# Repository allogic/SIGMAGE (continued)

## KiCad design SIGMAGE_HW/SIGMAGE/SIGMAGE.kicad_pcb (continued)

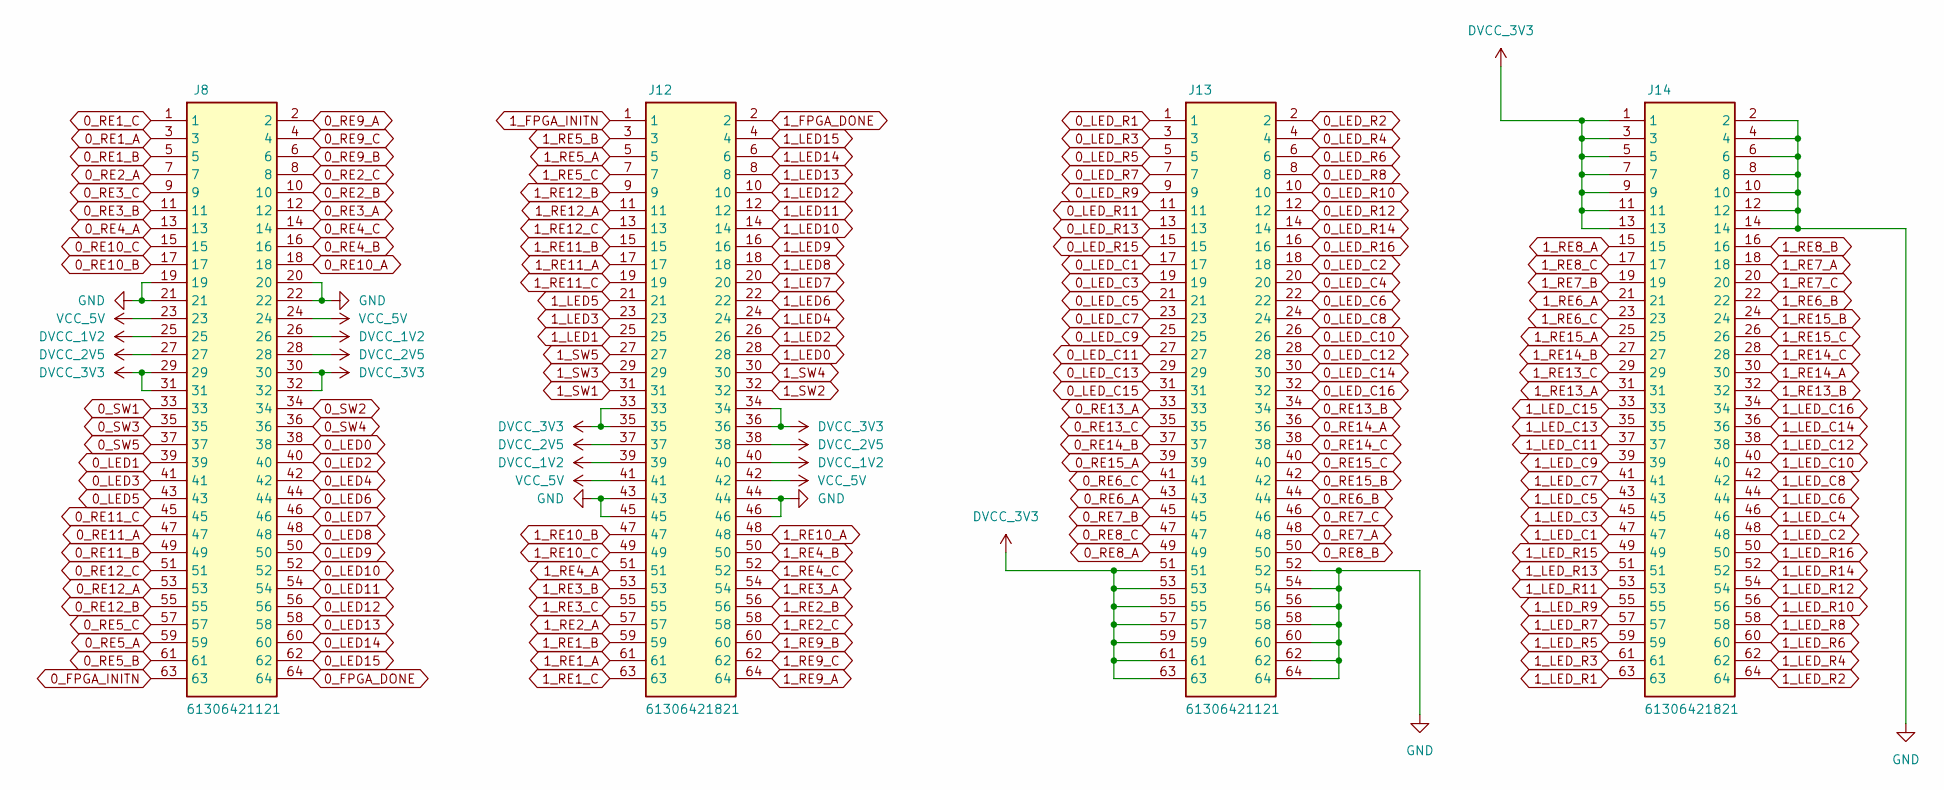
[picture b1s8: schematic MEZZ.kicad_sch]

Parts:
J8, J13: 61306421121; Manufacturer_Part_Number 61306421121; Mouser Part Number 710-61306421121
J12, J14: 61306421821; Manufacturer_Part_Number 61306421821; Mouser Part Number 710-61306421821

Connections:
0_FPGA_DONE: J8.64; also elsewhere on the board
0_FPGA_INITN: J8.63; also elsewhere on the board
0_LED0: J8.38; also elsewhere on the board
0_LED1: J8.39; also elsewhere on the board
0_LED2: J8.40; also elsewhere on the board
0_LED3: J8.41; also elsewhere on the board
0_LED4: J8.42; also elsewhere on the board
0_LED5: J8.43; also elsewhere on the board
0_LED6: J8.44; also elsewhere on the board
0_LED7: J8.46; also elsewhere on the board
0_LED8: J8.48; also elsewhere on the board
0_LED9: J8.50; also elsewhere on the board
0_LED10: J8.52; also elsewhere on the board
0_LED11: J8.54; also elsewhere on the board
0_LED12: J8.56; also elsewhere on the board
0_LED13: J8.58; also elsewhere on the board
0_LED14: J8.60; also elsewhere on the board
0_LED15: J8.62; also elsewhere on the board
0_LED_C1: J13.17; also elsewhere on the board
0_LED_C2: J13.18; also elsewhere on the board
0_LED_C3: J13.19; also elsewhere on the board
0_LED_C4: J13.20; also elsewhere on the board
0_LED_C5: J13.21; also elsewhere on the board
0_LED_C6: J13.22; also elsewhere on the board
0_LED_C7: J13.23; also elsewhere on the board
0_LED_C8: J13.24; also elsewhere on the board
0_LED_C9: J13.25; also elsewhere on the board
0_LED_C10: J13.26; also elsewhere on the board
0_LED_C11: J13.27; also elsewhere on the board
0_LED_C12: J13.28; also elsewhere on the board
0_LED_C13: J13.29; also elsewhere on the board
0_LED_C14: J13.30; also elsewhere on the board
0_LED_C15: J13.31; also elsewhere on the board
0_LED_C16: J13.32; also elsewhere on the board
0_LED_R1: J13.1; also elsewhere on the board
0_LED_R2: J13.2; also elsewhere on the board
0_LED_R3: J13.3; also elsewhere on the board
0_LED_R4: J13.4; also elsewhere on the board
0_LED_R5: J13.5; also elsewhere on the board
0_LED_R6: J13.6; also elsewhere on the board
0_LED_R7: J13.7; also elsewhere on the board
0_LED_R8: J13.8; also elsewhere on the board
0_LED_R9: J13.9; also elsewhere on the board
0_LED_R10: J13.10; also elsewhere on the board
0_LED_R11: J13.11; also elsewhere on the board
0_LED_R12: J13.12; also elsewhere on the board
0_LED_R13: J13.13; also elsewhere on the board
0_LED_R14: J13.14; also elsewhere on the board
0_LED_R15: J13.15; also elsewhere on the board
0_LED_R16: J13.16; also elsewhere on the board
0_RE1_A: J8.3; also elsewhere on the board
0_RE1_B: J8.5; also elsewhere on the board
0_RE1_C: J8.1; also elsewhere on the board
0_RE2_A: J8.7; also elsewhere on the board
0_RE2_B: J8.10; also elsewhere on the board
0_RE2_C: J8.8; also elsewhere on the board
0_RE3_A: J8.12; also elsewhere on the board
0_RE3_B: J8.11; also elsewhere on the board
0_RE3_C: J8.9; also elsewhere on the board
0_RE4_A: J8.13; also elsewhere on the board
0_RE4_B: J8.16; also elsewhere on the board
0_RE4_C: J8.14; also elsewhere on the board
0_RE5_A: J8.59; also elsewhere on the board
0_RE5_B: J8.61; also elsewhere on the board
0_RE5_C: J8.57; also elsewhere on the board
0_RE6_A: J13.43; also elsewhere on the board
0_RE6_B: J13.44; also elsewhere on the board
0_RE6_C: J13.41; also elsewhere on the board
0_RE7_A: J13.48; also elsewhere on the board
0_RE7_B: J13.45; also elsewhere on the board
0_RE7_C: J13.46; also elsewhere on the board
0_RE8_A: J13.49; also elsewhere on the board
0_RE8_B: J13.50; also elsewhere on the board
0_RE8_C: J13.47; also elsewhere on the board
0_RE9_A: J8.2; also elsewhere on the board
0_RE9_B: J8.6; also elsewhere on the board
0_RE9_C: J8.4; also elsewhere on the board
0_RE10_A: J8.18; also elsewhere on the board
0_RE10_B: J8.17; also elsewhere on the board
0_RE10_C: J8.15; also elsewhere on the board
0_RE11_A: J8.47; also elsewhere on the board
0_RE11_B: J8.49; also elsewhere on the board
0_RE11_C: J8.45; also elsewhere on the board
0_RE12_A: J8.53; also elsewhere on the board
0_RE12_B: J8.55; also elsewhere on the board
0_RE12_C: J8.51; also elsewhere on the board
0_RE13_A: J13.33; also elsewhere on the board
0_RE13_B: J13.34; also elsewhere on the board
0_RE13_C: J13.35; also elsewhere on the board
0_RE14_A: J13.36; also elsewhere on the board
0_RE14_B: J13.37; also elsewhere on the board
0_RE14_C: J13.38; also elsewhere on the board
0_RE15_A: J13.39; also elsewhere on the board
0_RE15_B: J13.42; also elsewhere on the board
0_RE15_C: J13.40; also elsewhere on the board
0_SW1: J8.33; also elsewhere on the board
0_SW2: J8.34; also elsewhere on the board
0_SW3: J8.35; also elsewhere on the board
0_SW4: J8.36; also elsewhere on the board
0_SW5: J8.37; also elsewhere on the board
1_FPGA_DONE: J12.2; also elsewhere on the board
1_FPGA_INITN: J12.1; also elsewhere on the board
1_LED0: J12.28; also elsewhere on the board
1_LED1: J12.25; also elsewhere on the board
1_LED2: J12.26; also elsewhere on the board
1_LED3: J12.23; also elsewhere on the board
1_LED4: J12.24; also elsewhere on the board
1_LED5: J12.21; also elsewhere on the board
1_LED6: J12.22; also elsewhere on the board
1_LED7: J12.20; also elsewhere on the board
1_LED8: J12.18; also elsewhere on the board
1_LED9: J12.16; also elsewhere on the board
1_LED10: J12.14; also elsewhere on the board
1_LED11: J12.12; also elsewhere on the board
1_LED12: J12.10; also elsewhere on the board
1_LED13: J12.8; also elsewhere on the board
1_LED14: J12.6; also elsewhere on the board
1_LED15: J12.4; also elsewhere on the board
1_LED_C1: J14.47; also elsewhere on the board
1_LED_C2: J14.48; also elsewhere on the board
1_LED_C3: J14.45; also elsewhere on the board
1_LED_C4: J14.46; also elsewhere on the board
1_LED_C5: J14.43; also elsewhere on the board
1_LED_C6: J14.44; also elsewhere on the board
1_LED_C7: J14.41; also elsewhere on the board
1_LED_C8: J14.42; also elsewhere on the board
1_LED_C9: J14.39; also elsewhere on the board
1_LED_C10: J14.40; also elsewhere on the board
1_LED_C11: J14.37; also elsewhere on the board
1_LED_C12: J14.38; also elsewhere on the board
1_LED_C13: J14.35; also elsewhere on the board
1_LED_C14: J14.36; also elsewhere on the board
1_LED_C15: J14.33; also elsewhere on the board
1_LED_C16: J14.34; also elsewhere on the board
1_LED_R1: J14.63; also elsewhere on the board
1_LED_R2: J14.64; also elsewhere on the board
1_LED_R3: J14.61; also elsewhere on the board
1_LED_R4: J14.62; also elsewhere on the board
1_LED_R5: J14.59; also elsewhere on the board
1_LED_R6: J14.60; also elsewhere on the board
1_LED_R7: J14.57; also elsewhere on the board
1_LED_R8: J14.58; also elsewhere on the board
1_LED_R9: J14.55; also elsewhere on the board
1_LED_R10: J14.56; also elsewhere on the board
1_LED_R11: J14.53; also elsewhere on the board
1_LED_R12: J14.54; also elsewhere on the board
1_LED_R13: J14.51; also elsewhere on the board
1_LED_R14: J14.52; also elsewhere on the board
1_LED_R15: J14.49; also elsewhere on the board
1_LED_R16: J14.50; also elsewhere on the board
1_RE1_A: J12.61; also elsewhere on the board
1_RE1_B: J12.59; also elsewhere on the board
1_RE1_C: J12.63; also elsewhere on the board
1_RE2_A: J12.57; also elsewhere on the board
1_RE2_B: J12.56; also elsewhere on the board
1_RE2_C: J12.58; also elsewhere on the board
1_RE3_A: J12.54; also elsewhere on the board
1_RE3_B: J12.53; also elsewhere on the board
1_RE3_C: J12.55; also elsewhere on the board
1_RE4_A: J12.51; also elsewhere on the board
1_RE4_B: J12.50; also elsewhere on the board
1_RE4_C: J12.52; also elsewhere on the board
1_RE5_A: J12.5; also elsewhere on the board
1_RE5_B: J12.3; also elsewhere on the board
1_RE5_C: J12.7; also elsewhere on the board
1_RE6_A: J14.21; also elsewhere on the board
1_RE6_B: J14.22; also elsewhere on the board
1_RE6_C: J14.23; also elsewhere on the board
1_RE7_A: J14.18; also elsewhere on the board
1_RE7_B: J14.19; also elsewhere on the board
1_RE7_C: J14.20; also elsewhere on the board
1_RE8_A: J14.15; also elsewhere on the board
1_RE8_B: J14.16; also elsewhere on the board
1_RE8_C: J14.17; also elsewhere on the board
1_RE9_A: J12.64; also elsewhere on the board
1_RE9_B: J12.60; also elsewhere on the board
1_RE9_C: J12.62; also elsewhere on the board
1_RE10_A: J12.48; also elsewhere on the board
1_RE10_B: J12.47; also elsewhere on the board
1_RE10_C: J12.49; also elsewhere on the board
1_RE11_A: J12.17; also elsewhere on the board
1_RE11_B: J12.15; also elsewhere on the board
1_RE11_C: J12.19; also elsewhere on the board
1_RE12_A: J12.11; also elsewhere on the board
1_RE12_B: J12.9; also elsewhere on the board
1_RE12_C: J12.13; also elsewhere on the board
1_RE13_A: J14.31; also elsewhere on the board
1_RE13_B: J14.32; also elsewhere on the board
1_RE13_C: J14.29; also elsewhere on the board
1_RE14_A: J14.30; also elsewhere on the board
1_RE14_B: J14.27; also elsewhere on the board
1_RE14_C: J14.28; also elsewhere on the board
1_RE15_A: J14.25; also elsewhere on the board
1_RE15_B: J14.24; also elsewhere on the board
1_RE15_C: J14.26; also elsewhere on the board
1_SW1: J12.31; also elsewhere on the board
1_SW2: J12.32; also elsewhere on the board
1_SW3: J12.29; also elsewhere on the board
1_SW4: J12.30; also elsewhere on the board
1_SW5: J12.27; also elsewhere on the board
DVCC_1V2: J8.25, J8.26, J12.39, J12.40; also elsewhere on the board
DVCC_2V5: J8.27, J8.28, J12.37, J12.38; also elsewhere on the board
DVCC_3V3: J8.29, J8.30, J8.31, J8.32, J12.33, J12.34, J12.35, J12.36, J13.51, J13.53, J13.55, J13.57, J13.59, J13.61, J13.63, J14.1, J14.3, J14.5, J14.7, J14.9, J14.11, J14.13; also elsewhere on the board
GND: J8.19, J8.20, J8.21, J8.22, J12.43, J12.44, J12.45, J12.46, J13.52, J13.54, J13.56, J13.58, J13.60, J13.62, J13.64, J14.2, J14.4, J14.6, J14.8, J14.10, J14.12, J14.14; also elsewhere on the board

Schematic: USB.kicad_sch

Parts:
C10, C11: 2.2u; C_0603_1608Metric
C33, C35: 4700n; C_0603_1608Metric
C34, C36, C38, C39, C40, C41, C42, C43, C44, C46: 100n; C_0603_1608Metric
C37, C45: 10u; C_0603_1608Metric
C47, C48: 18p; C_0603_1608Metric
CR1: 7M12MAAJT
D4: LED; LED_0603_1608Metric
FB4: 500 @ 100 MHz; C_0603_1608Metric
FB6, FB7: 600 @ 100 MHz; C_0603_1608Metric
J1: UJ31CHG2SMTTR; Manufacturer_Part_Number UJ31-CH-G2-SMT-TR; Mouser Part Number 490-UJ31-CH-G2SMT-TR
J3, J6: TSW10607GS
R10, R11: 5k1; R_0603_1608Metric
R12: 1500; R_0603_1608Metric
R22, R26, R27: 10k; R_0603_1608Metric
R28, R29, R30, R31, R59, R60, R61, R62: 4700; R_0603_1608Metric
R41, R43: 12k; R_0603_1608Metric
R42: 2200; R_0603_1608Metric
U9: FT2232HLTRAY; FT2232HTRAY
U13: ESDR0502NMUTBG
U14: 93LC56-I/SN; 93LC56ISN

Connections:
0_FPGA_JTAG_TCK: J3.5, R28.2, U9.16 (ADBUS0); also elsewhere on the board
0_FPGA_JTAG_TDI: J3.4, R29.1, U9.17 (ADBUS1); also elsewhere on the board
0_FPGA_JTAG_TDO: J3.3, R30.1, U9.18 (ADBUS2); also elsewhere on the board
0_FPGA_JTAG_TMS: J3.2, R31.1, U9.19 (ADBUS3); also elsewhere on the board
0_MCU_JTAG_TCK: J6.5, R60.2, U9.38 (BDBUS0); also elsewhere on the board
0_MCU_JTAG_TDI: J6.4, R59.1, U9.39 (BDBUS1); also elsewhere on the board
0_MCU_JTAG_TDO: J6.3, R61.1, U9.40 (BDBUS2); also elsewhere on the board
0_MCU_JTAG_TMS: J6.2, R62.1, U9.41 (BDBUS3); also elsewhere on the board
0_USB_DN: J1.A7 (DN1), J1.B7 (DN2), U9.7 (DM), U13.3 (NC), U13.4 (D-)
0_USB_DP: J1.A6 (DP1), J1.B6 (DP2), U9.8 (DP), U13.2 (NC), U13.5 (D+)
DVCCFT_1V8: C37.1, C38.1, C39.1, C40.1, U9.12 (VCORE), U9.37 (VCORE), U9.49 (VREGOUT), U9.64 (VCORE)
DVCC_3V3: C41.1, C42.1, C43.1, C44.1, C45.1, C46.1, FB6.1, FB7.1, J3.1, J6.1, R22.2, R26.2, R27.2, R29.2, R30.2, R31.2, R42.1, R59.2, R61.2, R62.2, U9.20 (VCCIO), U9.31 (VCCIO), U9.42 (VCCIO), U9.50 (VREGIN), U9.56 (VCCIO), U14.6 (ORG), U14.8 (VCC); also elsewhere on the board
GND: C10.2, C11.2, C33.2, C34.2, C35.2, C36.2, C37.2, C38.2, C39.2, C40.2, C41.2, C42.2, C43.2, C44.2, C45.2, C46.2, C47.2, C48.2, CR1.2, CR1.4, D4.1 (K), J1.A1 (GND_1), J1.A12 (GND_2), J1.B1 (GND_3), J1.B12 (GND_4), J1.S1 (GND_5), J1.S2 (GND_6), J1.S3 (GND_7), J1.S4 (GND_8), J3.6, J6.6, R10.2, R11.2, R28.1, R41.1, R60.1, U9.1 (GND), U9.5 (GND), U9.10 (AGND), U9.11 (GND), U9.13 (TEST), U9.15 (GND), U9.25 (GND), U9.35 (GND), U9.47 (GND), U9.51 (GND), U13.1 (GND), U14.5 (VSS); also elsewhere on the board
unnamed: D4.2 (A), R12.2
unnamed: J1.A5 (CC1), R10.1
unnamed: J1.B5 (CC2), R11.1
unnamed: C47.1, CR1.1, U9.2 (OSCI)
unnamed: C48.1, CR1.3, U9.3 (OSCO)
unnamed: R41.2, U9.6 (REF)
unnamed: R42.2, U9.14 (RESET#)
unnamed: C33.1, C34.1, FB6.2, U9.4 (VPHY)
unnamed: C35.1, C36.1, FB7.2, U9.9 (VPLL)
unnamed: R26.1, U9.62 (EECLK), U14.2 (CLK)
unnamed: R22.1, U9.63 (EECS), U14.1 (CS)
unnamed: R43.2, U9.61 (EEDATA), U14.3 (DI)
unnamed: R27.1, R43.1, U14.4 (DO)

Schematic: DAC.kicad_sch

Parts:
C58, C60, C66, C68, C72, C73, C76, C77, C145, C146, C147, C148, C153, C154, C155, C156: 10u; C_0603_1608Metric
C59, C61, C67, C69, C74, C75, C78, C79, C149, C150, C151, C152, C157, C158, C159, C160: 100n; C_0603_1608Metric
C62, C63, C82, C83, C165, C166, C167, C168: 1u; C_0603_1608Metric
C64, C65, C80, C81, C161, C162, C163, C164: 2200n; C_0603_1608Metric
C70, C71, C84, C85, C169, C170, C171, C172: 1n; C_0603_1608Metric
J20, J21, J24, J25: SJ63073E; Manufacturer_Part_Number SJ-63073E; Mouser Part Number 490-SJ-63073E
R33, R34, R39, R40, R63, R64, R65, R66: 6500; R_0603_1608Metric
R35, R36, R37, R38, R52, R53, R54, R55: 1M; R_0603_1608Metric
U3, U10, U20, U21: PCM5102APWR

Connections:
0_BUS_DAC_BCK: U3.13 (BCK), U10.13 (BCK), U20.13 (BCK), U21.13 (BCK); also elsewhere on the board
0_BUS_DAC_LRCK: U3.15 (LRCK), U10.15 (LRCK), U20.15 (LRCK), U21.15 (LRCK); also elsewhere on the board
0_BUS_DAC_SCK: U3.12 (SCK), U10.12 (SCK), U20.12 (SCK), U21.12 (SCK); also elsewhere on the board
0_DAC1_DIN: U3.14 (DIN); also elsewhere on the board
0_DAC1_FLT: U3.11 (FLT); also elsewhere on the board
0_DAC1_XSMT: U3.17 (XSMT); also elsewhere on the board
0_DAC2_DIN: U10.14 (DIN); also elsewhere on the board
0_DAC2_FLT: U10.11 (FLT); also elsewhere on the board
0_DAC2_XSMT: U10.17 (XSMT); also elsewhere on the board
0_DAC3_DIN: U20.14 (DIN); also elsewhere on the board
0_DAC3_FLT: U20.11 (FLT); also elsewhere on the board
0_DAC3_XSMT: U20.17 (XSMT); also elsewhere on the board
0_DAC4_DIN: U21.14 (DIN); also elsewhere on the board
0_DAC4_FLT: U21.11 (FLT); also elsewhere on the board
0_DAC4_XSMT: U21.17 (XSMT); also elsewhere on the board
AVCC_3V3: C66.1, C67.1, C68.1, C69.1, C72.1, C73.1, C74.1, C75.1, C145.1, C146.1, C147.1, C148.1, C149.1, C150.1, C151.1, C152.1, U3.1 (CPVDD), U3.8 (AVDD), U10.1 (CPVDD), U10.8 (AVDD), U20.1 (CPVDD), U20.8 (AVDD), U21.1 (CPVDD), U21.8 (AVDD); also elsewhere on the board
DVCC_3V3: C60.1, C61.1, C77.1, C79.1, C154.1, C156.1, C158.1, C160.1, U3.20 (DVDD), U10.20 (DVDD), U20.20 (DVDD), U21.20 (DVDD); also elsewhere on the board
GND: C58.2, C59.2, C60.2, C61.2, C65.2, C66.2, C67.2, C68.2, C69.2, C70.2, C71.2, C72.2, C73.2, C74.2, C75.2, C76.2, C77.2, C78.2, C79.2, C81.2, C84.2, C85.2, C145.2, C146.2, C147.2, C148.2, C149.2, C150.2, C151.2, C152.2, C153.2, C154.2, C155.2, C156.2, C157.2, C158.2, C159.2, C160.2, C162.2, C164.2, C169.2, C170.2, C171.2, C172.2, J20.1 (SLEEVE), J21.1 (SLEEVE), J24.1 (SLEEVE), J25.1 (SLEEVE), R35.1, R36.1, R37.1, R38.1, R52.1, R53.1, R54.1, R55.1, U3.3 (CPGND), U3.9 (AGND), U3.10 (DEMP), U3.16 (FMT), U3.19 (DGND), U10.3 (CPGND), U10.9 (AGND), U10.10 (DEMP), U10.16 (FMT), U10.19 (DGND), U20.3 (CPGND), U20.9 (AGND), U20.10 (DEMP), U20.16 (FMT), U20.19 (DGND), U21.3 (CPGND), U21.9 (AGND), U21.10 (DEMP), U21.16 (FMT), U21.19 (DGND); also elsewhere on the board
unnamed: C62.2, R33.1, R35.2
unnamed: C63.2, R34.1, R36.2
unnamed: C82.2, R37.2, R39.1
unnamed: C83.2, R38.2, R40.1
unnamed: C165.2, R52.2, R63.1
unnamed: C166.2, R53.2, R64.1
unnamed: C167.2, R54.2, R65.1
unnamed: C168.2, R55.2, R66.1
unnamed: C71.1, J20.3 (RING), R34.2
unnamed: C70.1, J20.2 (TIP), R33.2
unnamed: C85.1, J21.3 (RING), R40.2
unnamed: C84.1, J21.2 (TIP), R39.2
unnamed: C170.1, J24.3 (RING), R64.2
unnamed: C169.1, J24.2 (TIP), R63.2
unnamed: C172.1, J25.3 (RING), R66.2
unnamed: C171.1, J25.2 (TIP), R65.2
unnamed: C64.2, U3.4 (CAPM)
unnamed: C64.1, U3.2 (CAPP)
unnamed: C58.1, C59.1, U3.18 (LDOO)
unnamed: C62.1, U3.6 (OUTL)
unnamed: C63.1, U3.7 (OUTR)
unnamed: C65.1, U3.5 (VNEG)
unnamed: C80.2, U10.4 (CAPM)
unnamed: C80.1, U10.2 (CAPP)
unnamed: C76.1, C78.1, U10.18 (LDOO)
unnamed: C82.1, U10.6 (OUTL)
unnamed: C83.1, U10.7 (OUTR)
unnamed: C81.1, U10.5 (VNEG)
unnamed: C161.2, U20.4 (CAPM)
unnamed: C161.1, U20.2 (CAPP)
unnamed: C153.1, C157.1, U20.18 (LDOO)
unnamed: C165.1, U20.6 (OUTL)
unnamed: C166.1, U20.7 (OUTR)
unnamed: C162.1, U20.5 (VNEG)
unnamed: C163.2, U21.4 (CAPM)
unnamed: C163.1, U21.2 (CAPP)
unnamed: C155.1, C159.1, U21.18 (LDOO)
unnamed: C167.1, U21.6 (OUTL)
unnamed: C168.1, U21.7 (OUTR)
unnamed: C164.1, U21.5 (VNEG)

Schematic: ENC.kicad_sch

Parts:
R67, R68, R69, R70, R71, R72, R73, R74, R75, R76, R77, R78, R79, R80, R81, R82, R83, R84, R85, R86, R87, R88, R89, R90, R117, R118, R119, R120, R121, R122, R123, R124, R125, R126, R127, R128, R129, R130, R131, R132, R133, R134, R135, R136, R137: 10k; R_0603_1608Metric
U22, U23, U24, U25, U26, U27, U28, U29, U30, U32, U33, U34, U35, U36, U37: EC11E183440C; Manufacturer_Part_Number EC11E183440C; Mouser Part Number 688-EC11E183440C

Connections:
1_RE1_A: R67.1, U22.A1; also elsewhere on the board
1_RE1_B: R68.1, U22.B1; also elsewhere on the board
1_RE1_C: R69.1, U22.D1; also elsewhere on the board
1_RE2_A: R70.1, U23.A1; also elsewhere on the board
1_RE2_B: R72.1, U23.B1; also elsewhere on the board
1_RE2_C: R71.1, U23.D1; also elsewhere on the board
1_RE3_A: R73.1, U24.A1; also elsewhere on the board
1_RE3_B: R75.1, U24.B1; also elsewhere on the board
1_RE3_C: R74.1, U24.D1; also elsewhere on the board
1_RE4_A: R76.1, U25.A1; also elsewhere on the board
1_RE4_B: R78.1, U25.B1; also elsewhere on the board
1_RE4_C: R77.1, U25.D1; also elsewhere on the board
1_RE5_A: R79.1, U26.A1; also elsewhere on the board
1_RE5_B: R81.1, U26.B1; also elsewhere on the board
1_RE5_C: R80.1, U26.D1; also elsewhere on the board
1_RE6_A: R82.1, U27.A1; also elsewhere on the board
1_RE6_B: R84.1, U27.B1; also elsewhere on the board
1_RE6_C: R83.1, U27.D1; also elsewhere on the board
1_RE7_A: R85.1, U28.A1; also elsewhere on the board
1_RE7_B: R87.1, U28.B1; also elsewhere on the board
1_RE7_C: R86.1, U28.D1; also elsewhere on the board
1_RE8_A: R88.1, U29.A1; also elsewhere on the board
1_RE8_B: R90.1, U29.B1; also elsewhere on the board
1_RE8_C: R89.1, U29.D1; also elsewhere on the board
1_RE9_A: R117.1, U30.A1; also elsewhere on the board
1_RE9_B: R119.1, U30.B1; also elsewhere on the board
1_RE9_C: R118.1, U30.D1; also elsewhere on the board
1_RE10_A: R120.1, U32.A1; also elsewhere on the board
1_RE10_B: R122.1, U32.B1; also elsewhere on the board
1_RE10_C: R121.1, U32.D1; also elsewhere on the board
1_RE11_A: R123.1, U33.A1; also elsewhere on the board
1_RE11_B: R125.1, U33.B1; also elsewhere on the board
1_RE11_C: R124.1, U33.D1; also elsewhere on the board
1_RE12_A: R126.1, U34.A1; also elsewhere on the board
1_RE12_B: R128.1, U34.B1; also elsewhere on the board
1_RE12_C: R127.1, U34.D1; also elsewhere on the board
1_RE13_A: R129.1, U35.A1; also elsewhere on the board
1_RE13_B: R131.1, U35.B1; also elsewhere on the board
1_RE13_C: R130.1, U35.D1; also elsewhere on the board
1_RE14_A: R132.1, U36.A1; also elsewhere on the board
1_RE14_B: R134.1, U36.B1; also elsewhere on the board
1_RE14_C: R133.1, U36.D1; also elsewhere on the board
1_RE15_A: R135.1, U37.A1; also elsewhere on the board
1_RE15_B: R137.1, U37.B1; also elsewhere on the board
1_RE15_C: R136.1, U37.D1; also elsewhere on the board
DVCC_3V3: R67.2, R68.2, R69.2, R70.2, R71.2, R72.2, R73.2, R74.2, R75.2, R76.2, R77.2, R78.2, R79.2, R80.2, R81.2, R82.2, R83.2, R84.2, R85.2, R86.2, R87.2, R88.2, R89.2, R90.2, R117.2, R118.2, R119.2, R120.2, R121.2, R122.2, R123.2, R124.2, R125.2, R126.2, R127.2, R128.2, R129.2, R130.2, R131.2, R132.2, R133.2, R134.2, R135.2, R136.2, R137.2; also elsewhere on the board
GND: U22.C1, U22.E1, U22.MH1, U22.MH2, U23.C1, U23.E1, U23.MH1, U23.MH2, U24.C1, U24.E1, U24.MH1, U24.MH2, U25.C1, U25.E1, U25.MH1, U25.MH2, U26.C1, U26.E1, U26.MH1, U26.MH2, U27.C1, U27.E1, U27.MH1, U27.MH2, U28.C1, U28.E1, U28.MH1, U28.MH2, U29.C1, U29.E1, U29.MH1, U29.MH2, U30.C1, U30.E1, U30.MH1, U30.MH2, U32.C1, U32.E1, U32.MH1, U32.MH2, U33.C1, U33.E1, U33.MH1, U33.MH2, U34.C1, U34.E1, U34.MH1, U34.MH2, U35.C1, U35.E1, U35.MH1, U35.MH2, U36.C1, U36.E1, U36.MH1, U36.MH2, U37.C1, U37.E1, U37.MH1, U37.MH2; also elsewhere on the board

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
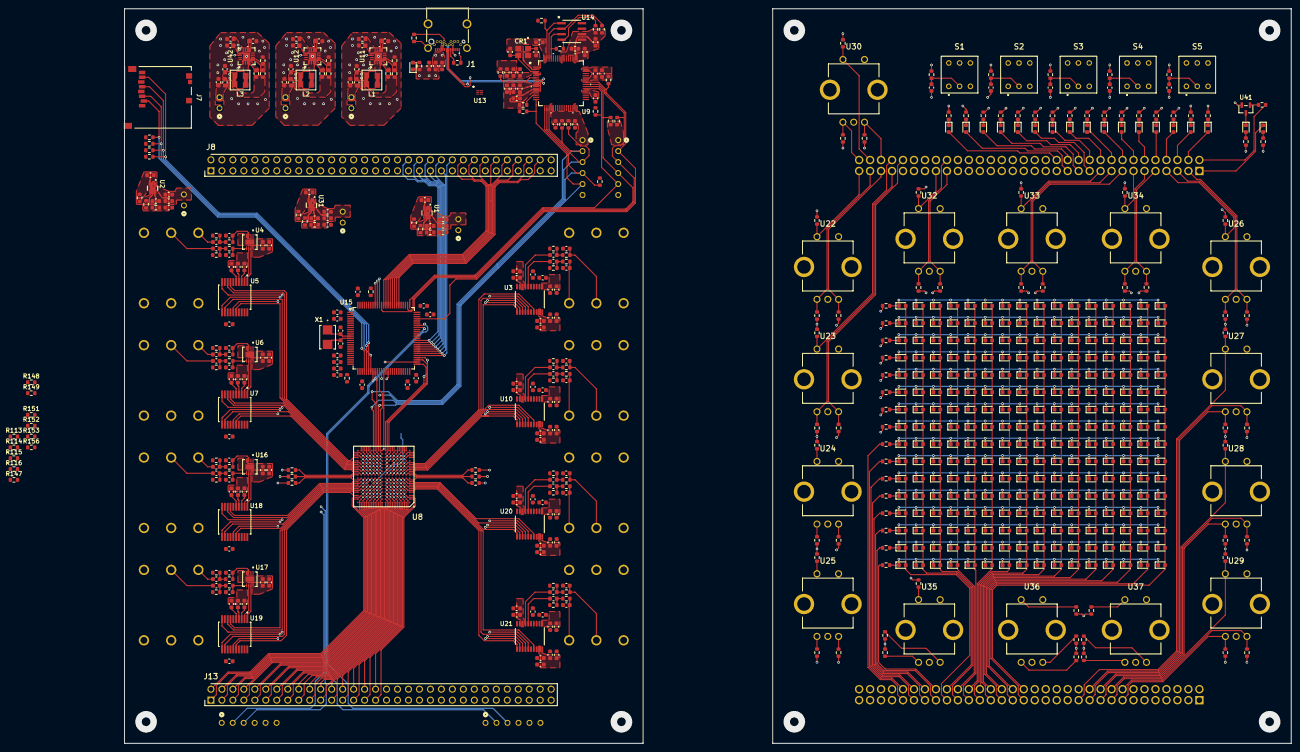
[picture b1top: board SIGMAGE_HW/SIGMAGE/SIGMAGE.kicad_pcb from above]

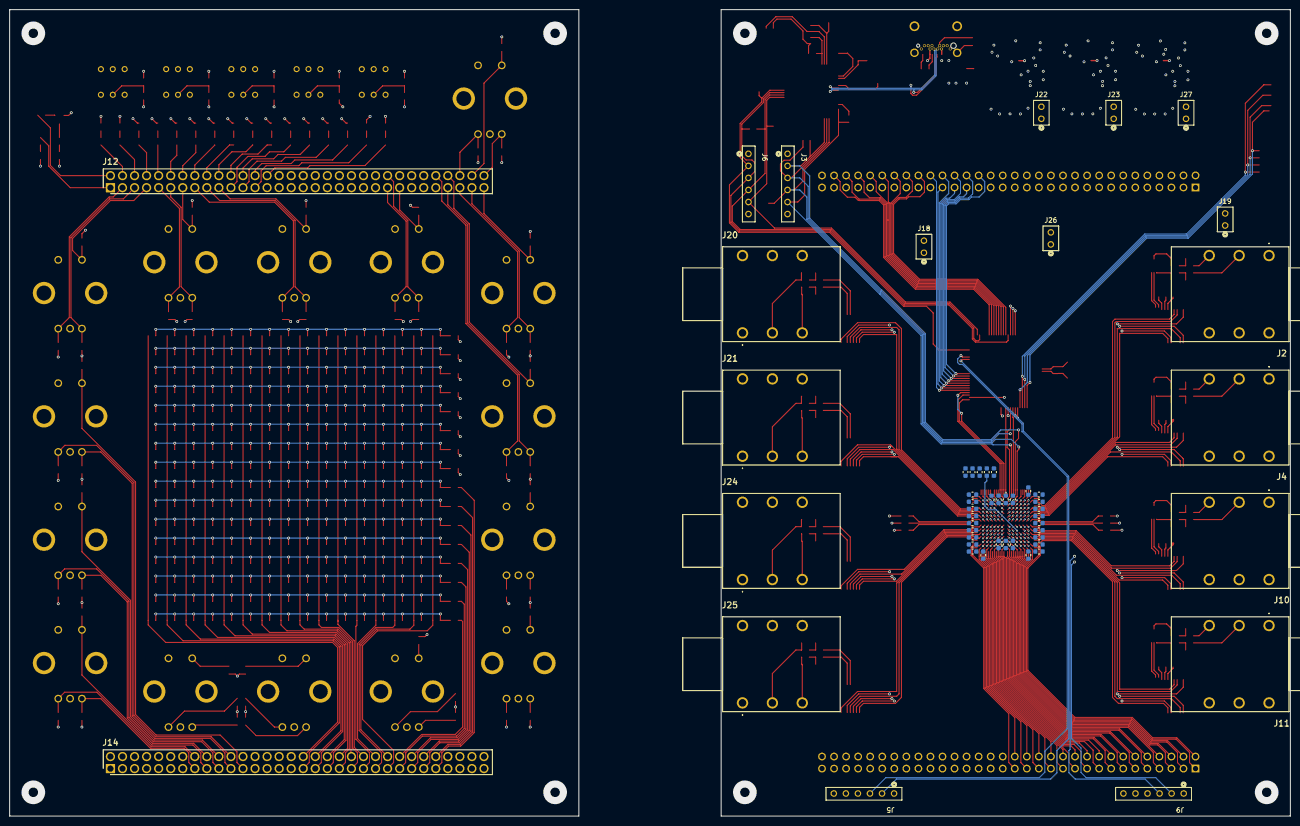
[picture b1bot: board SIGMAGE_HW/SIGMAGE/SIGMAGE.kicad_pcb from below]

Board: 6 copper layers, 270.0 x 170.0 mm, 725 parts (53 on the bottom side), 446 nets.

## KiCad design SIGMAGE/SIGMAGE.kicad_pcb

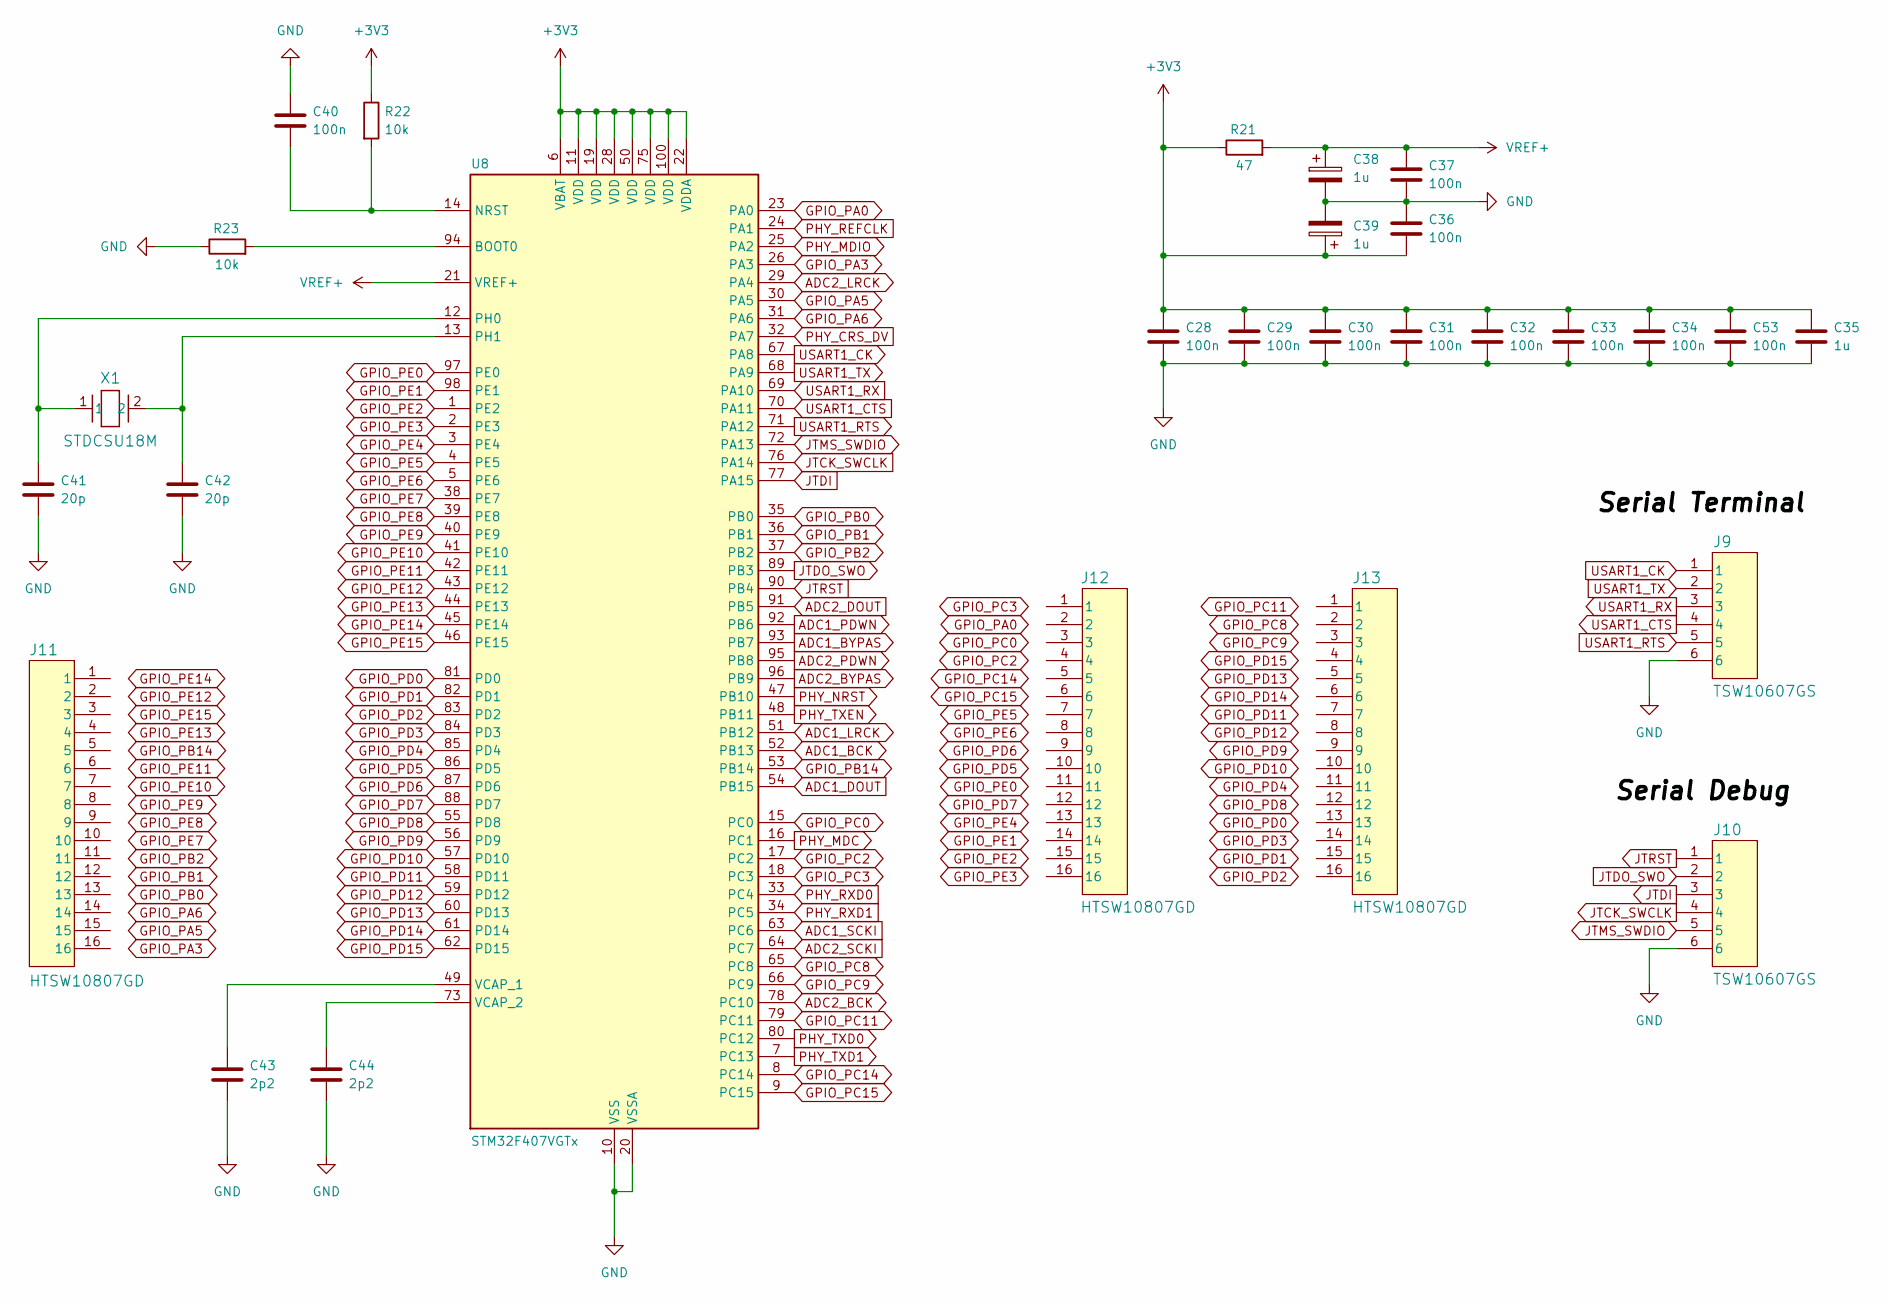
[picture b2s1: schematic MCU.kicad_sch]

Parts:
C28, C29, C30, C31, C32, C33, C34, C36, C37, C40, C53: 100n; C_0603_1608Metric
C35, C38, C39: 1u; C_0603_1608Metric
C41, C42: 20p; C_0603_1608Metric
C43, C44: 2p2; C_0603_1608Metric
J9, J10: TSW10607GS
J11, J12, J13: HTSW10807GD
R21: 47; R_0603_1608Metric
R22, R23: 10k; R_0603_1608Metric
U8: STM32F407VGTx; LQFP-100_14x14mm_P0.5mm
X1: STDCSU18M

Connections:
ADC1_BCK: U8.52 (PB13); also elsewhere on the board
ADC1_BYPAS: U8.93 (PB7); also elsewhere on the board
ADC1_DOUT: U8.54 (PB15); also elsewhere on the board
ADC1_LRCK: U8.51 (PB12); also elsewhere on the board
ADC1_PDWN: U8.92 (PB6); also elsewhere on the board
ADC1_SCKI: U8.63 (PC6); also elsewhere on the board
ADC2_BCK: U8.78 (PC10); also elsewhere on the board
ADC2_BYPAS: U8.96 (PB9); also elsewhere on the board
ADC2_DOUT: U8.91 (PB5); also elsewhere on the board
ADC2_LRCK: U8.29 (PA4); also elsewhere on the board
ADC2_PDWN: U8.95 (PB8); also elsewhere on the board
ADC2_SCKI: U8.64 (PC7); also elsewhere on the board
GND: C28.2, C29.2, C30.2, C31.2, C32.2, C33.2, C34.2, C35.2, C36.1, C37.2, C38.2, C39.2, C40.1, C41.2, C42.2, C43.2, C44.2, C53.2, J9.6, J10.6, R23.1, U8.10 (VSS), U8.20 (VSSA), U8.27 (VSS), U8.74 (VSS), U8.99 (VSS); also elsewhere on the board
GPIO_PA0: U8.23 (PA0)
GPIO_PA3: U8.26 (PA3)
GPIO_PA5: U8.30 (PA5)
GPIO_PA6: U8.31 (PA6)
GPIO_PB0: U8.35 (PB0)
GPIO_PB1: U8.36 (PB1)
GPIO_PB2: U8.37 (PB2)
GPIO_PB14: U8.53 (PB14)
GPIO_PC0: U8.15 (PC0)
GPIO_PC2: U8.17 (PC2)
GPIO_PC3: U8.18 (PC3)
GPIO_PC8: U8.65 (PC8)
GPIO_PC9: U8.66 (PC9)
GPIO_PC11: U8.79 (PC11)
GPIO_PC14: U8.8 (PC14)
GPIO_PC15: U8.9 (PC15)
GPIO_PD0: U8.81 (PD0)
GPIO_PD1: U8.82 (PD1)
GPIO_PD2: U8.83 (PD2)
GPIO_PD3: U8.84 (PD3)
GPIO_PD4: U8.85 (PD4)
GPIO_PD5: U8.86 (PD5)
GPIO_PD6: U8.87 (PD6)
GPIO_PD7: U8.88 (PD7)
GPIO_PD8: U8.55 (PD8)
GPIO_PD9: U8.56 (PD9)
GPIO_PD10: U8.57 (PD10)
GPIO_PD11: U8.58 (PD11)
GPIO_PD12: U8.59 (PD12)
GPIO_PD13: U8.60 (PD13)
GPIO_PD14: U8.61 (PD14)
GPIO_PD15: U8.62 (PD15)
GPIO_PE0: U8.97 (PE0)
GPIO_PE1: U8.98 (PE1)
GPIO_PE2: U8.1 (PE2)
GPIO_PE3: U8.2 (PE3)
GPIO_PE4: U8.3 (PE4)
GPIO_PE5: U8.4 (PE5)
GPIO_PE6: U8.5 (PE6)
GPIO_PE7: U8.38 (PE7)
GPIO_PE8: U8.39 (PE8)
GPIO_PE9: U8.40 (PE9)
GPIO_PE10: U8.41 (PE10)
GPIO_PE11: U8.42 (PE11)
GPIO_PE12: U8.43 (PE12)
GPIO_PE13: U8.44 (PE13)
GPIO_PE14: U8.45 (PE14)
GPIO_PE15: U8.46 (PE15)
JTCK_SWCLK: J10.4, U8.76 (PA14)
JTDI: J10.3, U8.77 (PA15)
JTDO_SWO: J10.2, U8.89 (PB3)
JTMS_SWDIO: J10.5, U8.72 (PA13)
JTRST: J10.1, U8.90 (PB4)
unnamed: R23.2, U8.94 (BOOT0)
unnamed: C40.2, R22.2, U8.14 (NRST)
unnamed: C41.1, U8.12 (PH0), X1.1
unnamed: C42.1, U8.13 (PH1), X1.2
unnamed: C43.1, U8.49 (VCAP_1)
unnamed: C44.1, U8.73 (VCAP_2)
PHY_CRS_DV: U8.32 (PA7); also elsewhere on the board
PHY_MDC: U8.16 (PC1); also elsewhere on the board
PHY_MDIO: U8.25 (PA2); also elsewhere on the board
PHY_NRST: U8.47 (PB10); also elsewhere on the board
PHY_REFCLK: U8.24 (PA1); also elsewhere on the board
PHY_RXD0: U8.33 (PC4); also elsewhere on the board
PHY_RXD1: U8.34 (PC5); also elsewhere on the board
PHY_TXD0: U8.80 (PC12); also elsewhere on the board
PHY_TXD1: U8.7 (PC13); also elsewhere on the board
PHY_TXEN: U8.48 (PB11); also elsewhere on the board
USART1_CK: J9.1, U8.67 (PA8)
USART1_CTS: J9.4, U8.70 (PA11)
USART1_RTS: J9.5, U8.71 (PA12)
USART1_RX: J9.3, U8.69 (PA10)
USART1_TX: J9.2, U8.68 (PA9)
VREF+: C37.1, C38.1, R21.2, U8.21 (VREF+)
